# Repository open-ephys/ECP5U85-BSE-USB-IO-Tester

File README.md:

# IO Tester for the Open Ephys ECP5U85-BSE-USB Development Board

- Used in concert with test gateware on FPGA
- Tests all IO and power exposed through the BSE headers

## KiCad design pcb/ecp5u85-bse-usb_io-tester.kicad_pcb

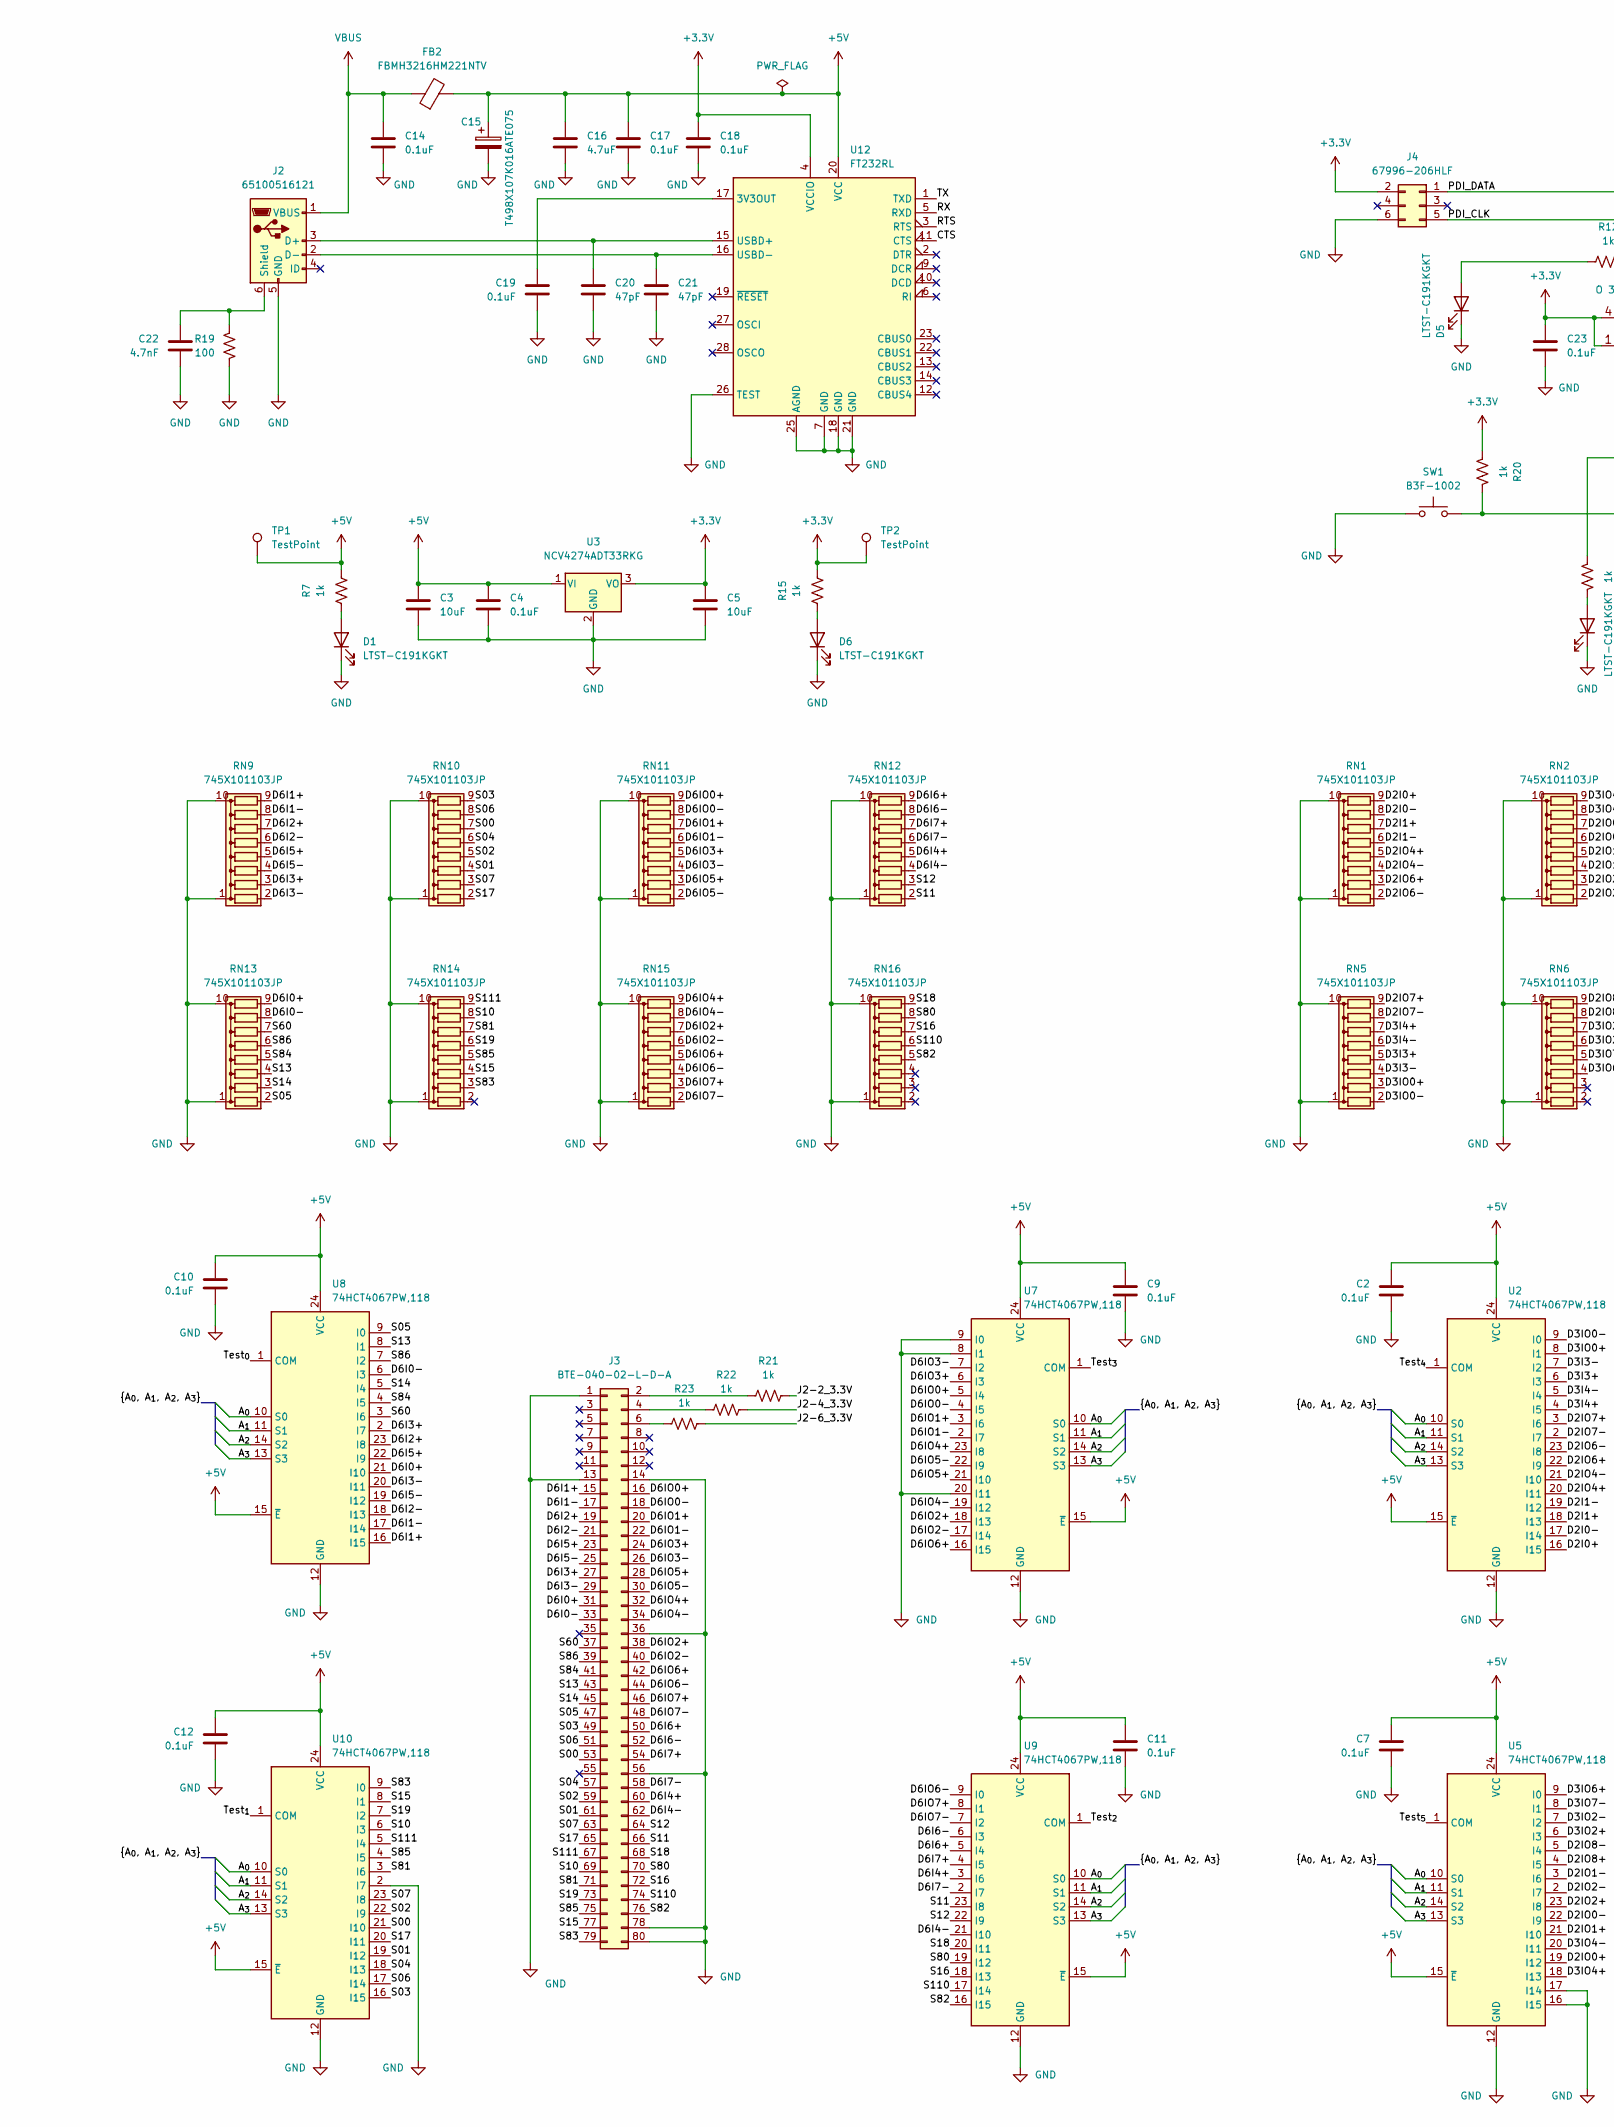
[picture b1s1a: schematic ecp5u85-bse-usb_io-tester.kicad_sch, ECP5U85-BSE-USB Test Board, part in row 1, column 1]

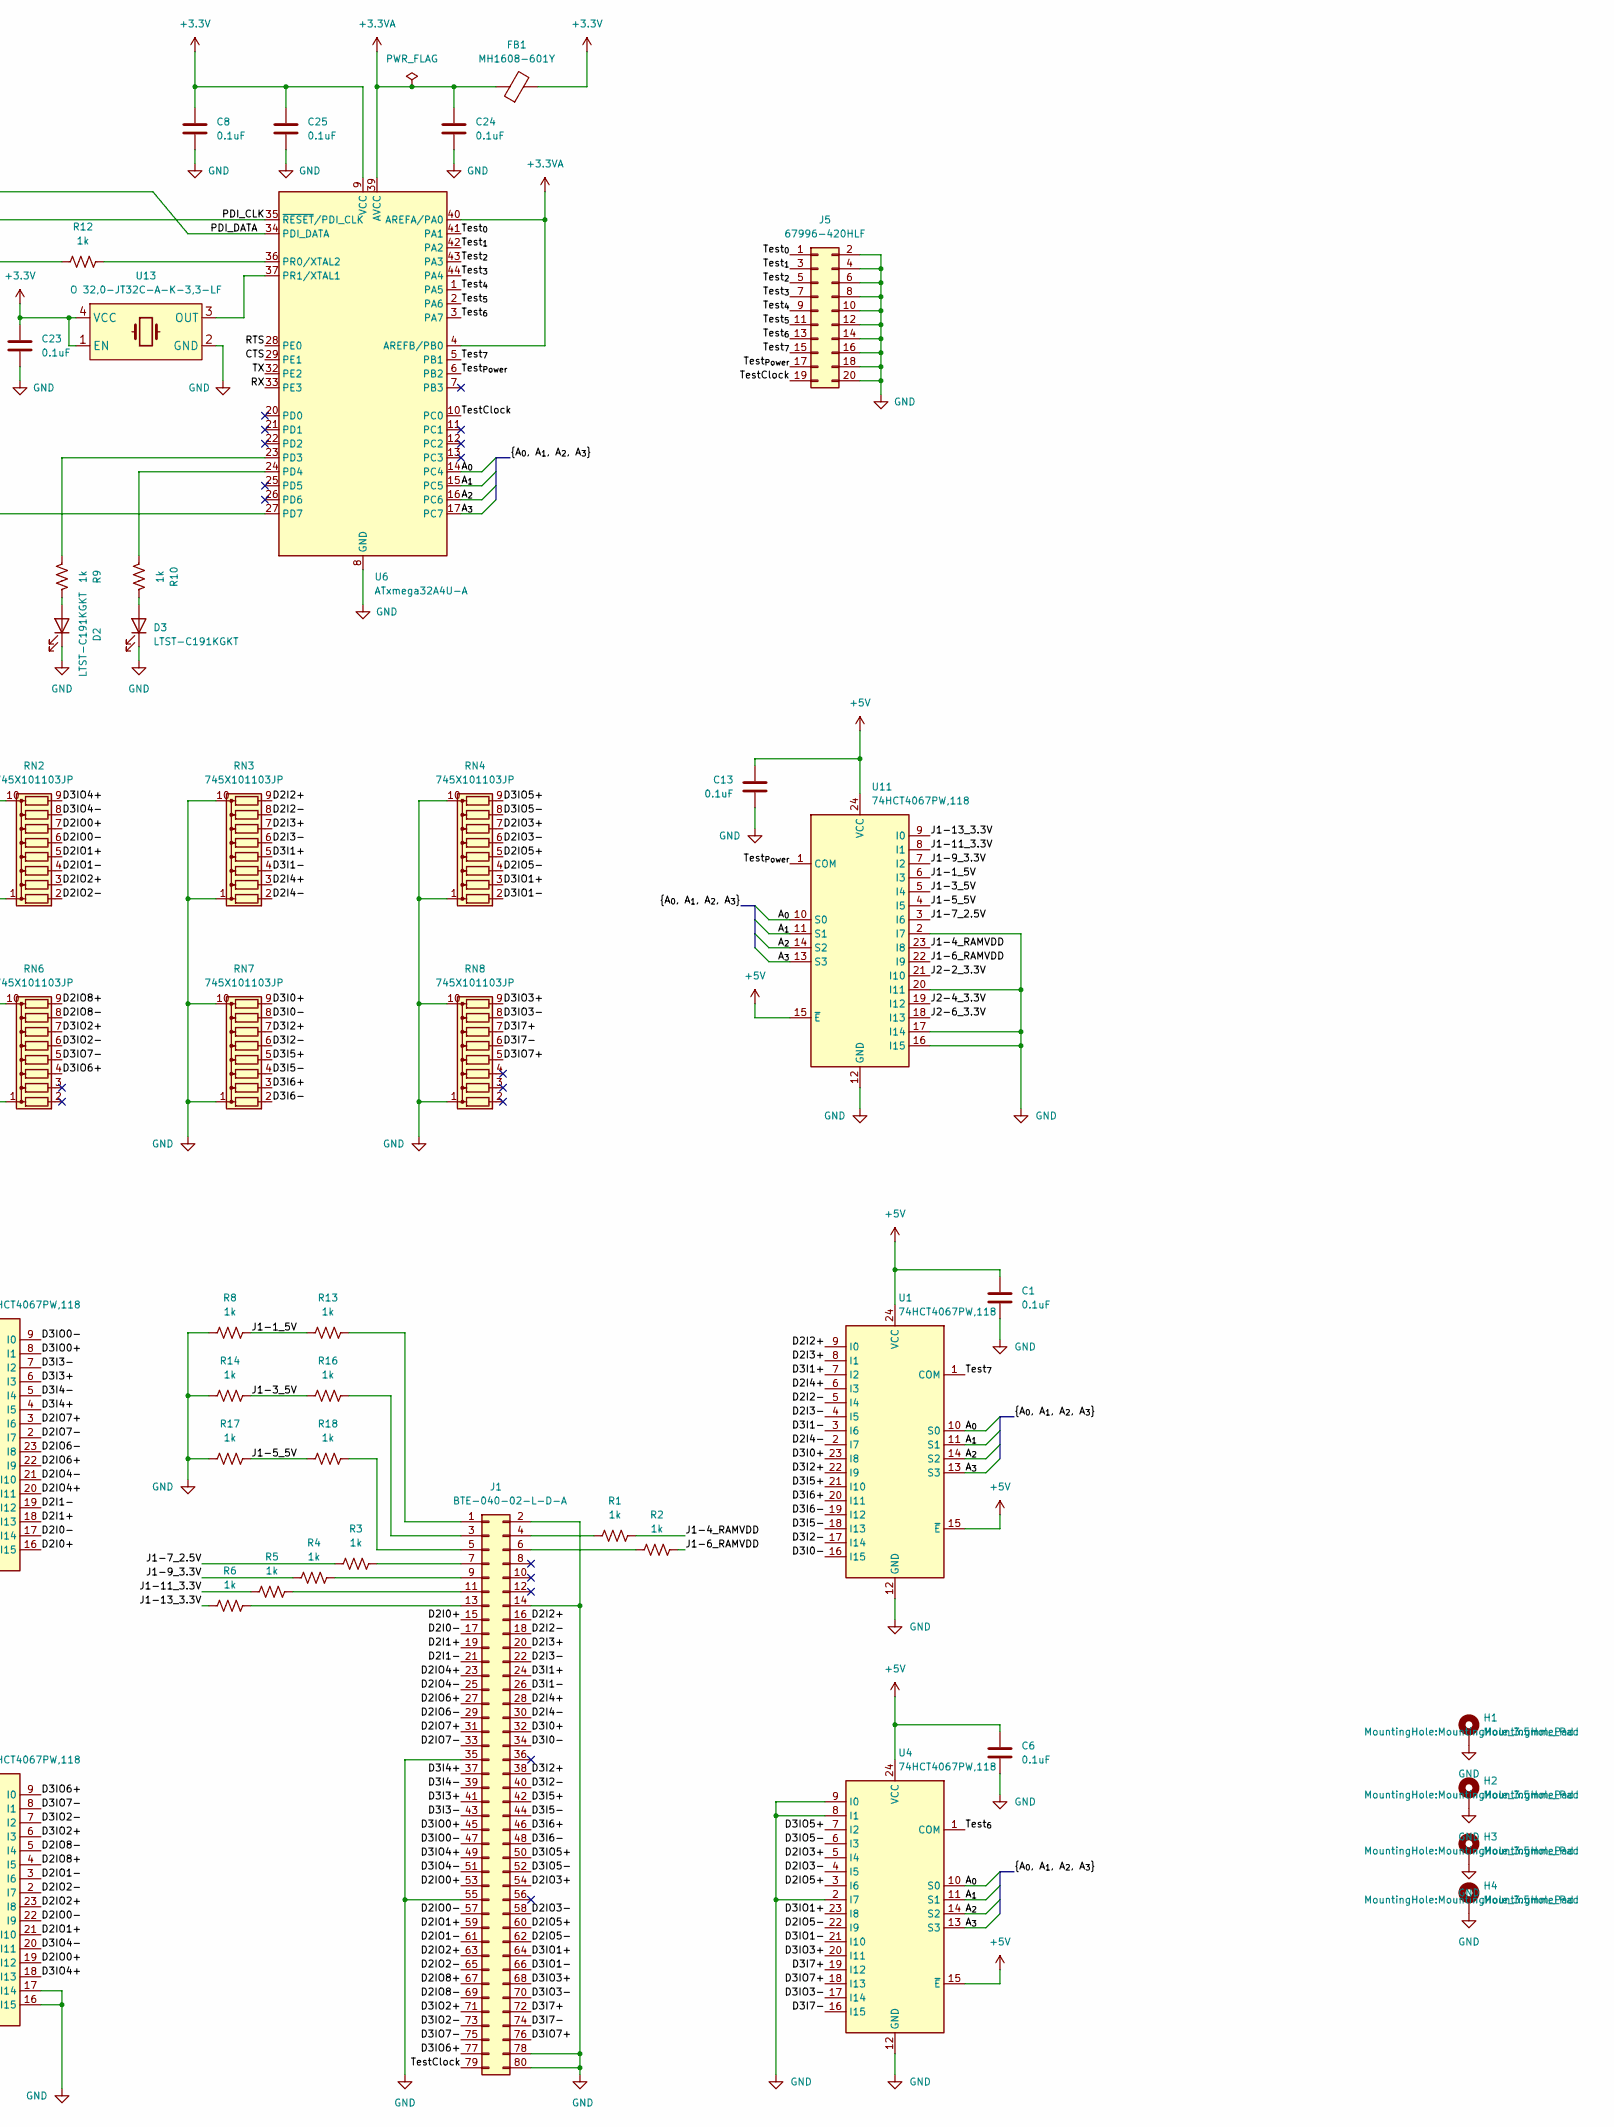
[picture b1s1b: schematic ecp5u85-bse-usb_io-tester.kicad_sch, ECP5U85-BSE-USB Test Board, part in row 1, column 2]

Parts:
C1, C2, C6, C7, C9, C10, C11, C12, C13: 0.1uF; C_0402_1005Metric
C3, C5: 10uF; C_1210_3225Metric
C4, C8, C14, C17, C18, C19, C23, C24, C25: 0.1uF; C_0603_1608Metric
C15: T498X107K016ATE075; CP_EIA-7343-20_Kemet-V
C16: 4.7uF; C_0805_2012Metric
C20, C21: 47pF; C_0603_1608Metric
C22: 4.7nF; C_0603_1608Metric
D1, D2, D3, D5, D6: LTST-C191KGKT; LED_0603_1608Metric
FB1: MH1608-601Y; L_0603_1608Metric
FB2: FBMH3216HM221NTV; L_1206_3216Metric
H1, H2, H3, H4: MountingHole_Pad; MountingHole_3.5mm_Pad
J1, J3: BTE-040-02-L-D-A; SAMTEC_BTE-040-01-L-D-A-K-TR
J2: 65100516121; USB_Mini-B_Wuerth_65100516121_Horizontal
J4: 67996-206HLF; PinHeader_2x03_P2.54mm_Vertical
J5: 67996-420HLF; PinHeader_2x10_P2.54mm_Vertical
R1, R2, R3, R4, R5, R6, R7, R8, R9, R10, R12, R13, R14, R15, R16, R17, R18, R20, R21, R22, R23: 1k; R_0402_1005Metric
R19: 100; R_0402_1005Metric
RN1, RN2, RN3, RN4, RN5, RN6, RN7, RN8, RN9, RN10, RN11, RN12, RN13, RN14, RN15, RN16: 745X101103JP; CTS_745X101
SW1: B3F-1002; SW_PUSH_6mm_H8mm
TP1, TP2: TestPoint; TestPoint_THTPad_3.0x3.0mm_Drill1.5mm
U1, U2, U4, U5, U7, U8, U9, U10, U11: 74HCT4067PW,118; TSSOP-24_4.4x7.8mm_P0.65mm
U3: NCV4274ADT33RKG; TO-252-2
U6: ATxmega32A4U-A; TQFP-44_10x10mm_P0.8mm
U12: FT232RL; SSOP-28_5.3x10.2mm_P0.65mm
U13: O 32,0-JT32C-A-K-3,3-LF; Oscillator_SMD_Abracon_ASE-4Pin_3.2x2.5mm

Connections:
+3.3VA: C24.1, FB1.1, U6.4 (AREFB/PB0), U6.39 (AVCC), U6.40 (AREFA/PA0)
+3V3: C5.1, C8.1, C18.1, C23.1, C25.1, FB1.2, J4.2, R15.2, R20.2, TP2.1, U3.3 (VO), U6.9 (VCC), U6.19 (VCC), U6.31 (VCC), U12.4 (VCCIO), U13.1 (EN), U13.4 (VCC)
+5V: C1.1, C2.1, C3.1, C4.1, C6.1, C7.1, C9.1, C10.1, C11.1, C12.1, C13.1, C15.1, C16.1, C17.1, FB2.2, R7.2, TP1.1, U1.15 (~E), U1.24 (VCC), U2.15 (~E), U2.24 (VCC), U3.1 (VI), U4.15 (~E), U4.24 (VCC), U5.15 (~E), U5.24 (VCC), U7.15 (~E), U7.24 (VCC), U8.15 (~E), U8.24 (VCC), U9.15 (~E), U9.24 (VCC), U10.15 (~E), U10.24 (VCC), U11.15 (~E), U11.24 (VCC), U12.20 (VCC)
/A_{0}: U1.10 (S0), U2.10 (S0), U4.10 (S0), U5.10 (S0), U6.14 (PC4), U7.10 (S0), U8.10 (S0), U9.10 (S0), U10.10 (S0), U11.10 (S0)
/A_{1}: U1.11 (S1), U2.11 (S1), U4.11 (S1), U5.11 (S1), U6.15 (PC5), U7.11 (S1), U8.11 (S1), U9.11 (S1), U10.11 (S1), U11.11 (S1)
/A_{2}: U1.14 (S2), U2.14 (S2), U4.14 (S2), U5.14 (S2), U6.16 (PC6), U7.14 (S2), U8.14 (S2), U9.14 (S2), U10.14 (S2), U11.14 (S2)
/A_{3}: U1.13 (S3), U2.13 (S3), U4.13 (S3), U5.13 (S3), U6.17 (PC7), U7.13 (S3), U8.13 (S3), U9.13 (S3), U10.13 (S3), U11.13 (S3)
/CTS: U6.29 (PE1), U12.11 (CTS)
/D2I0+: J1.15, RN1.9 (R8), U2.16 (I15)
/D2I0-: J1.17, RN1.8 (R7), U2.17 (I14)
/D2I1+: J1.19, RN1.7 (R6), U2.18 (I13)
/D2I1-: J1.21, RN1.6 (R5), U2.19 (I12)
/D2I2+: J1.16, RN3.9 (R8), U1.9 (I0)
/D2I2-: J1.18, RN3.8 (R7), U1.5 (I4)
/D2I3+: J1.20, RN3.7 (R6), U1.8 (I1)
/D2I3-: J1.22, RN3.6 (R5), U1.4 (I5)
/D2I4+: J1.28, RN3.3 (R2), U1.6 (I3)
/D2I4-: J1.30, RN3.2 (R1), U1.2 (I7)
/D2IO0+: J1.53, RN2.7 (R6), U5.19 (I12)
/D2IO0-: J1.57, RN2.6 (R5), U5.22 (I9)
/D2IO1+: J1.59, RN2.5 (R4), U5.21 (I10)
/D2IO1-: J1.61, RN2.4 (R3), U5.3 (I6)
/D2IO2+: J1.63, RN2.3 (R2), U5.23 (I8)
/D2IO2-: J1.65, RN2.2 (R1), U5.2 (I7)
/D2IO3+: J1.54, RN4.7 (R6), U4.5 (I4)
/D2IO3-: J1.58, RN4.6 (R5), U4.4 (I5)
/D2IO4+: J1.23, RN1.5 (R4), U2.20 (I11)
/D2IO4-: J1.25, RN1.4 (R3), U2.21 (I10)
/D2IO5+: J1.60, RN4.5 (R4), U4.3 (I6)
/D2IO5-: J1.62, RN4.4 (R3), U4.22 (I9)
/D2IO6+: J1.27, RN1.3 (R2), U2.22 (I9)
/D2IO6-: J1.29, RN1.2 (R1), U2.23 (I8)
/D2IO7+: J1.31, RN5.9 (R8), U2.3 (I6)
/D2IO7-: J1.33, RN5.8 (R7), U2.2 (I7)
/D2IO8+: J1.67, RN6.9 (R8), U5.4 (I5)
/D2IO8-: J1.69, RN6.8 (R7), U5.5 (I4)
/D3I0+: J1.32, RN7.9 (R8), U1.23 (I8)
/D3I0-: J1.34, RN7.8 (R7), U1.16 (I15)
/D3I1+: J1.24, RN3.5 (R4), U1.7 (I2)
/D3I1-: J1.26, RN3.4 (R3), U1.3 (I6)
/D3I2+: J1.38, RN7.7 (R6), U1.22 (I9)
/D3I2-: J1.40, RN7.6 (R5), U1.17 (I14)
/D3I3+: J1.41, RN5.5 (R4), U2.6 (I3)
/D3I3-: J1.43, RN5.4 (R3), U2.7 (I2)
/D3I4+: J1.37, RN5.7 (R6), U2.4 (I5)
/D3I4-: J1.39, RN5.6 (R5), U2.5 (I4)
/D3I5+: J1.42, RN7.5 (R4), U1.21 (I10)
/D3I5-: J1.44, RN7.4 (R3), U1.18 (I13)
/D3I6+: J1.46, RN7.3 (R2), U1.20 (I11)
/D3I6-: J1.48, RN7.2 (R1), U1.19 (I12)
/D3I7+: J1.72, RN8.7 (R6), U4.19 (I12)
/D3I7-: J1.74, RN8.6 (R5), U4.16 (I15)
/D3IO0+: J1.45, RN5.3 (R2), U2.8 (I1)
/D3IO0-: J1.47, RN5.2 (R1), U2.9 (I0)
/D3IO1+: J1.64, RN4.3 (R2), U4.23 (I8)
/D3IO1-: J1.66, RN4.2 (R1), U4.21 (I10)
/D3IO2+: J1.71, RN6.7 (R6), U5.6 (I3)
/D3IO2-: J1.73, RN6.6 (R5), U5.7 (I2)
/D3IO3+: J1.68, RN8.9 (R8), U4.20 (I11)
/D3IO3-: J1.70, RN8.8 (R7), U4.17 (I14)
/D3IO4+: J1.49, RN2.9 (R8), U5.18 (I13)
/D3IO4-: J1.51, RN2.8 (R7), U5.20 (I11)
/D3IO5+: J1.50, RN4.9 (R8), U4.7 (I2)
/D3IO5-: J1.52, RN4.8 (R7), U4.6 (I3)
/D3IO6+: J1.77, RN6.4 (R3), U5.9 (I0)
/D3IO7+: J1.76, RN8.5 (R4), U4.18 (I13)
/D3IO7-: J1.75, RN6.5 (R4), U5.8 (I1)
/D6I0+: J3.31, RN13.9 (R8), U8.21 (I10)
/D6I0-: J3.33, RN13.8 (R7), U8.6 (I3)
/D6I1+: J3.15, RN9.9 (R8), U8.16 (I15)
/D6I1-: J3.17, RN9.8 (R7), U8.17 (I14)
/D6I2+: J3.19, RN9.7 (R6), U8.23 (I8)
/D6I2-: J3.21, RN9.6 (R5), U8.18 (I13)
/D6I3+: J3.27, RN9.3 (R2), U8.2 (I7)
/D6I3-: J3.29, RN9.2 (R1), U8.20 (I11)
/D6I4+: J3.60, RN12.5 (R4), U9.3 (I6)
/D6I4-: J3.62, RN12.4 (R3), U9.21 (I10)
/D6I5+: J3.23, RN9.5 (R4), U8.22 (I9)
/D6I5-: J3.25, RN9.4 (R3), U8.19 (I12)
/D6I6+: J3.50, RN12.9 (R8), U9.5 (I4)
/D6I6-: J3.52, RN12.8 (R7), U9.6 (I3)
/D6I7+: J3.54, RN12.7 (R6), U9.4 (I5)
/D6I7-: J3.58, RN12.6 (R5), U9.2 (I7)
/D6IO0+: J3.16, RN11.9 (R8), U7.5 (I4)
/D6IO0-: J3.18, RN11.8 (R7), U7.4 (I5)
/D6IO1+: J3.20, RN11.7 (R6), U7.3 (I6)
/D6IO1-: J3.22, RN11.6 (R5), U7.2 (I7)
/D6IO2+: J3.38, RN15.7 (R6), U7.18 (I13)
/D6IO2-: J3.40, RN15.6 (R5), U7.17 (I14)
/D6IO3+: J3.24, RN11.5 (R4), U7.6 (I3)
/D6IO3-: J3.26, RN11.4 (R3), U7.7 (I2)
/D6IO4+: J3.32, RN15.9 (R8), U7.23 (I8)
/D6IO4-: J3.34, RN15.8 (R7), U7.19 (I12)
/D6IO5+: J3.28, RN11.3 (R2), U7.21 (I10)
/D6IO5-: J3.30, RN11.2 (R1), U7.22 (I9)
/D6IO6+: J3.42, RN15.5 (R4), U7.16 (I15)
/D6IO6-: J3.44, RN15.4 (R3), U9.9 (I0)
/D6IO7+: J3.46, RN15.3 (R2), U9.8 (I1)
/D6IO7-: J3.48, RN15.2 (R1), U9.7 (I2)
/J1-1_5V: R8.2, R13.1, U11.6 (I3)
/J1-3_5V: R14.2, R16.1, U11.5 (I4)
/J1-4_RAMVDD: R1.2, U11.23 (I8)
/J1-5_5V: R17.2, R18.1, U11.4 (I5)
/J1-6_RAMVDD: R2.2, U11.22 (I9)
/J1-7_2.5V: R3.1, U11.3 (I6)
/J1-9_3.3V: R4.1, U11.7 (I2)
/J1-11_3.3V: R5.1, U11.8 (I1)
/J1-13_3.3V: R6.1, U11.9 (I0)
/J2-2_3.3V: R21.2, U11.21 (I10)
/J2-4_3.3V: R22.2, U11.19 (I12)
/J2-6_3.3V: R23.2, U11.18 (I13)
/PDI_CLK: J4.5, U6.35 (~RESET/PDI_CLK)
/PDI_DATA: J4.1, U6.34 (PDI_DATA)
/RTS: U6.28 (PE0), U12.3 (RTS)
/RX: U6.33 (PE3), U12.5 (RXD)
/S00: J3.53, RN10.7 (R6), U10.21 (I10)
/S01: J3.61, RN10.4 (R3), U10.19 (I12)
/S02: J3.59, RN10.5 (R4), U10.22 (I9)
/S03: J3.49, RN10.9 (R8), U10.16 (I15)
/S04: J3.57, RN10.6 (R5), U10.18 (I13)
/S05: J3.47, RN13.2 (R1), U8.9 (I0)
/S06: J3.51, RN10.8 (R7), U10.17 (I14)
/S07: J3.63, RN10.3 (R2), U10.23 (I8)
/S10: J3.69, RN14.8 (R7), U10.6 (I3)
/S11: J3.66, RN12.2 (R1), U9.23 (I8)
/S12: J3.64, RN12.3 (R2), U9.22 (I9)
/S13: J3.43, RN13.4 (R3), U8.8 (I1)
/S14: J3.45, RN13.3 (R2), U8.5 (I4)
/S15: J3.77, RN14.4 (R3), U10.8 (I1)
/S16: J3.72, RN16.7 (R6), U9.18 (I13)
/S17: J3.65, RN10.2 (R1), U10.20 (I11)
/S18: J3.68, RN16.9 (R8), U9.20 (I11)
/S19: J3.73, RN14.6 (R5), U10.7 (I2)
/S60: J3.37, RN13.7 (R6), U8.3 (I6)
/S80: J3.70, RN16.8 (R7), U9.19 (I12)
/S81: J3.71, RN14.7 (R6), U10.3 (I6)
/S82: J3.76, RN16.5 (R4), U9.16 (I15)
/S83: J3.79, RN14.3 (R2), U10.9 (I0)
/S84: J3.41, RN13.5 (R4), U8.4 (I5)
/S85: J3.75, RN14.5 (R4), U10.4 (I5)
/S86: J3.39, RN13.6 (R5), U8.7 (I2)
/S110: J3.74, RN16.6 (R5), U9.17 (I14)
/S111: J3.67, RN14.9 (R8), U10.5 (I4)
/TX: U6.32 (PE2), U12.1 (TXD)
/TestClock: J1.79, J5.19, U6.10 (PC0)
/Test_{0}: J5.1, U6.41 (PA1), U8.1 (COM)
/Test_{1}: J5.3, U6.42 (PA2), U10.1 (COM)
/Test_{2}: J5.5, U6.43 (PA3), U9.1 (COM)
/Test_{3}: J5.7, U6.44 (PA4), U7.1 (COM)
/Test_{4}: J5.9, U2.1 (COM), U6.1 (PA5)
/Test_{5}: J5.11, U5.1 (COM), U6.2 (PA6)
/Test_{6}: J5.13, U4.1 (COM), U6.3 (PA7)
/Test_{7}: J5.15, U1.1 (COM), U6.5 (PB1)
/Test_{Power}: J5.17, U6.6 (PB2), U11.1 (COM)
GND: C1.2, C2.2, C3.2, C4.2, C5.2, C6.2, C7.2, C8.2, C9.2, C10.2, C11.2, C12.2, C13.2, C14.2, C15.2, C16.2, C17.2, C18.2, C19.2, C20.2, C21.2, C22.2, C23.2, C24.2, C25.2, D1.1 (K), D2.1 (K), D3.1 (K), D5.1 (K), D6.1 (K), H1.1, H2.1, H3.1, H4.1, J1.2, J1.14, J1.35, J1.55, J1.78, J1.80, J2.5 (GND), J3.1, J3.13, J3.14, J3.36, J3.56, J3.78, J3.80, J4.6, J5.2, J5.4, J5.6, J5.8, J5.10, J5.12, J5.14, J5.16, J5.18, J5.20, R8.1, R14.1, R17.1, R19.1, RN1.1 (common), RN1.10 (common), RN2.1 (common), RN2.10 (common), RN3.1 (common), RN3.10 (common), RN4.1 (common), RN4.10 (common), RN5.1 (common), RN5.10 (common), RN6.1 (common), RN6.10 (common), RN7.1 (common), RN7.10 (common), RN8.1 (common), RN8.10 (common), RN9.1 (common), RN9.10 (common), RN10.1 (common), RN10.10 (common), RN11.1 (common), RN11.10 (common), RN12.1 (common), RN12.10 (common), RN13.1 (common), RN13.10 (common), RN14.1 (common), RN14.10 (common), RN15.1 (common), RN15.10 (common), RN16.1 (common), RN16.10 (common), SW1.2, U1.12 (GND), U2.12 (GND), U3.2 (GND), U4.2 (I7), U4.8 (I1), U4.9 (I0), U4.12 (GND), U5.12 (GND), U5.16 (I15), U5.17 (I14), U6.8 (GND), U6.18 (GND), U6.30 (GND), U6.38 (GND), U7.8 (I1), U7.9 (I0), U7.12 (GND), U7.20 (I11), U8.12 (GND), U9.12 (GND), U10.2 (I7), U10.12 (GND), U11.2 (I7), U11.12 (GND), U11.16 (I15), U11.17 (I14), U11.20 (I11), U12.7 (GND), U12.18 (GND), U12.21 (GND), U12.25 (AGND), U12.26 (TEST), U13.2 (GND)
unnamed: C19.1, U12.17 (3V3OUT)
unnamed: C20.1, J2.3 (D+), U12.15 (USBD+)
unnamed: C21.1, J2.2 (D-), U12.16 (USBD-)
unnamed: C22.1, J2.6 (Shield), R19.2
unnamed: D1.2 (A), R7.1
unnamed: D2.2 (A), R9.1
unnamed: D3.2 (A), R10.1
unnamed: D5.2 (A), R12.1
unnamed: D6.2 (A), R15.1
unnamed: J1.1, R13.2
unnamed: J1.3, R16.2
unnamed: J1.4, R1.1
unnamed: J1.5, R18.2
unnamed: J1.6, R2.1
unnamed: J1.7, R3.2
unnamed: J1.9, R4.2
unnamed: J1.11, R5.2
unnamed: J1.13, R6.2
unnamed: J3.2, R21.1
unnamed: J3.4, R22.1
unnamed: J3.6, R23.1
unnamed: R9.2, U6.23 (PD3)
unnamed: R10.2, U6.24 (PD4)
unnamed: R12.2, U6.36 (PR0/XTAL2)
unnamed: R20.1, SW1.1, U6.27 (PD7)
unnamed: U6.37 (PR1/XTAL1), U13.3 (OUT)
VBUS: C14.1, FB2.1, J2.1 (VBUS)

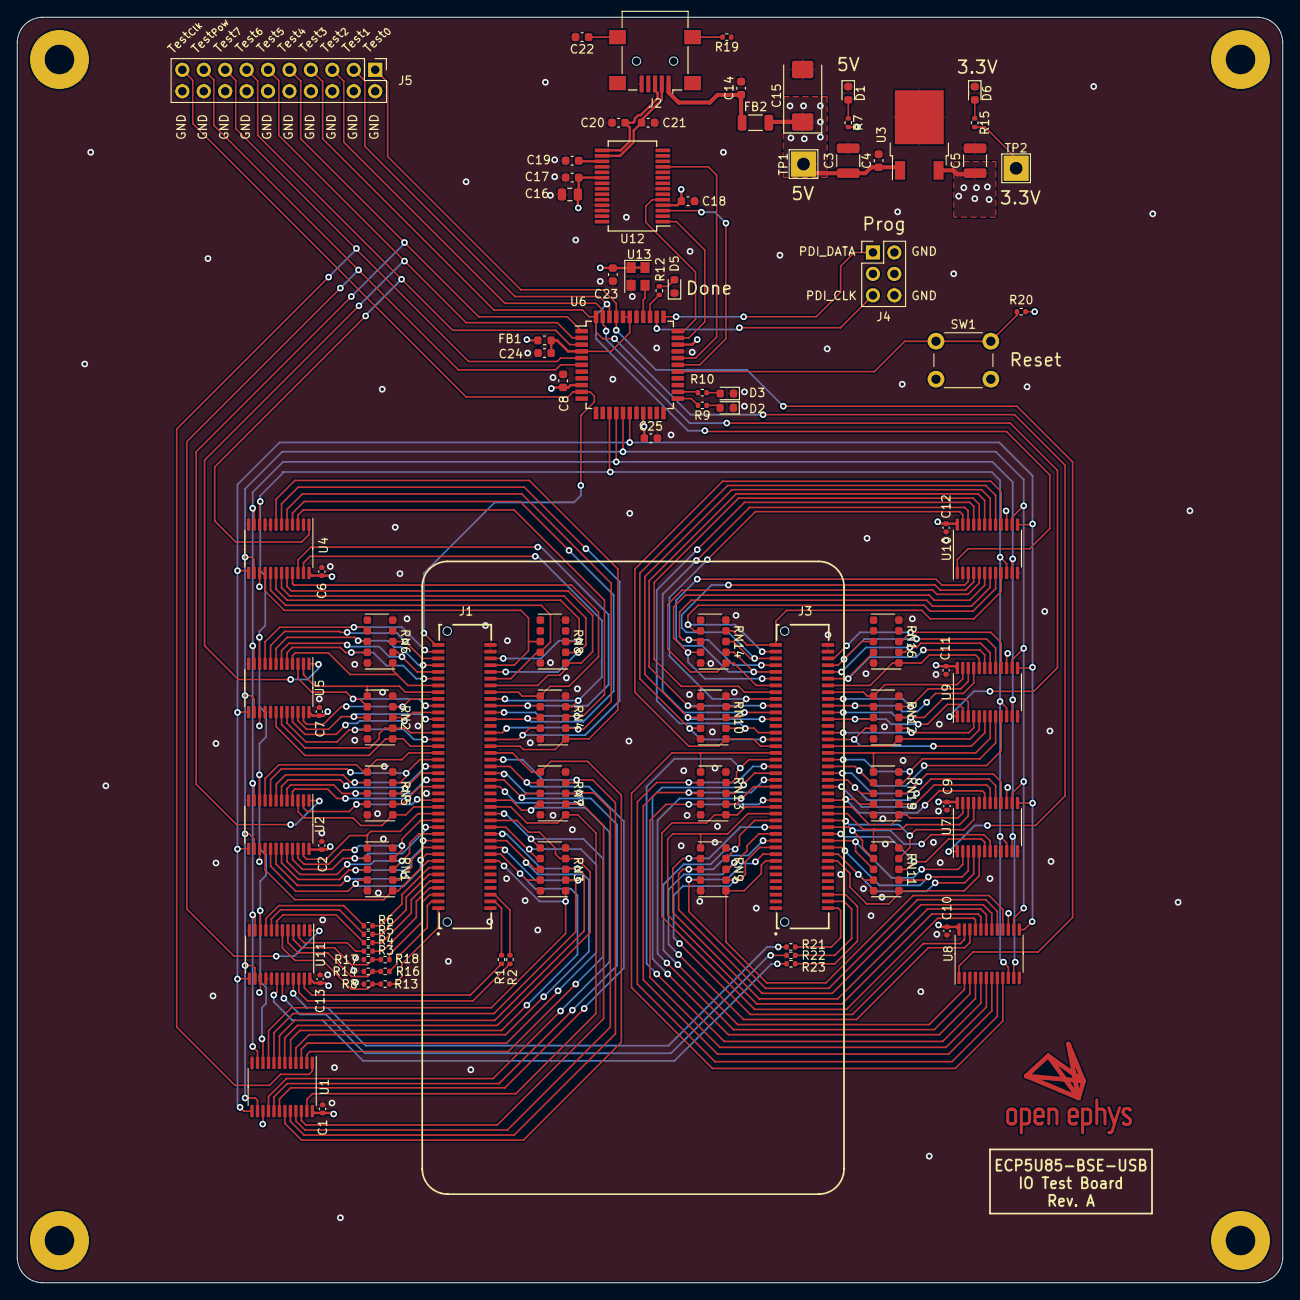
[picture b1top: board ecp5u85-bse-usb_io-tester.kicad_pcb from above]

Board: 4 copper layers, 150.0 x 150.0 mm, 95 parts (0 on the bottom side), 182 nets.

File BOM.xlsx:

# | References |  | Value | Footprint | Quantity
1 | C1, C2, C6, C7, C9, C10, C11, C12, C13 | OEPS010004 | 0.1uF | C_0402_1005Metric | 9
2 | C4, C8, C14, C17, C18, C19, C23, C24, C25 | OEPS010009 | 0.1uF | C_0603_1608Metric | 9
3 | C3, C5 | OEPS010010 | 10uF | C_1210_3225Metric | 2
4 | C20, C21 | OEPS010012 | 47pF | C_0603_1608Metric | 2
5 | C15 | OEPS210001 | T498X107K016ATE075 | CP_EIA-7343-20_Kemet-V | 1
6 | C16 | OEPS010013 | 4.7uF | C_0805_2012Metric | 1
7 | C22 | OEPS010014 | 4.7nF | C_0603_1608Metric | 1
8 | R1, R2, R3, R4, R5, R6, R7, R8, R9, R10, R12, R13, R14, R15, R16, R17, R18, R20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 | OEPS020006 | 1k | R_0402_1005Metric | 21
9 | R19 | OEPS020004 | 100 | R_0402_1005Metric | 1
10 | D1, D2, D3, D5, D6 | OEPS030005 | LTST-C191KGKT | LED_0603_1608Metric | 5
11 | U1, U2, U4, U5, U7, U8, U9, U10, U11 | OEPS080010 | 74HCT4067PW,118 | TSSOP-24_4.4x7.8mm_P0.65mm | 9
12 | U3 | OEPS080011 | NCV4274ADT33RKG | TO-252-2 | 1
13 | U6 | OEPS080012 | ATxmega32A4U-A | TQFP-44_10x10mm_P0.8mm | 1
14 | U12 | OEPS080013 | FT232RL | SSOP-28_5.3x10.2mm_P0.65mm | 1
15 | U13 | OEPS080014 | O 32,0-JT32C-A-K-3,3-LF | Oscillator_SMD_Abracon_ASE-4Pin_3.2x2.5mm | 1
16 | SW1 | OEPS100011 | B3F-1002 | SW_PUSH_6mm_H8mm | 1
17 | RN1, RN2, RN3, RN4, RN5, RN6, RN7, RN8, RN9, RN10, RN11, RN12, RN13, RN14, RN15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 | OEPS080015 | 745X101103JP | CTS_745X101 | 16
18 |  |  |  | OE-LOGO-14X10 | 1
19 | FB1 | OEPS040001 | MH1608-601Y | L_0603_1608Metric | 1
20 | FB2 | OEPS040002 | FBMH3216HM221NTV | L_1206_3216Metric | 1
21 | J1, J3 | OEPS070017 | BTE-040-02-L-D-A | SAMTEC_BTE-040-01-L-D-A-K-TR | 2
22 | J2 | OEPS070014 | 65100516121 | USB_Mini-B_Lumberg_2486_01_Horizontal | 1
23 | J4 | OEPS070015 | PR20203VBDN | PinHeader_2x03_P2.54mm_Vertical | 1
24 | J5 | OEPS070016 | 67996-420HLF | PinHeader_2x10_P2.54mm_Vertical | 1

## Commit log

2022-02-02 First commit of the schematic
2022-02-03 Add extra diode and update TODO
2022-02-03 Add filter and ESD protection to USB inputs
2022-02-09 Add FPGA oscillator
2022-02-09 Update libraries
2022-03-10 Update gitignore for #auto_save_files#
2022-07-06 Started IO test fixture
    - Feedback on circuit design needed
2022-08-29 Initial completed IO test board
    - Schematic and layout should be finished.
    - Will generate gerbers upon approval
2022-10-06 Remove submodule, upstate README.md
2022-10-06 Added fabrication files for Rev. A
    - SMD mounts are specified in smd-mount as CSV and in gerber as
    *-pnp_top.gbr and *-pnp-bottom.gbr
    - Fabrication information containing component reference designators and
    values are in gerber/*_Fab.gbr
    - The bill of materials is in bom folder. It can be exported to CSV in
    the browser application.
2022-10-06 Update pdf version of schematic
2022-10-24 Add tester gateware for the FPGA
2022-11-28 First commit (Harp structure, IOs, and registers).
2022-11-28 Implemented button handling.
2022-12-01 First full functional firmware.
2022-12-01 Added first draft of Bonsai workflow.
